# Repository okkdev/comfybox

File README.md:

# 

A stickless fighting game controller, intended to be more ergonomic compared to the regular stickless style layout.

## Features

- Split and 16° angled buttons for improved ergonomics
- Compatible with Kailh Choc v1/v2, Gateron Low Profile 1.0/2.0 and regular MX
- Completely reversible PCB for southpaw layout
- OLED screen
- Powered by [GP2040-CE](https://github.com/OpenStickCommunity/GP2040-CE)
  - Button remapping
  - SOCD Modes
  - XInput, DirectInput and Nintendo Switch
  - Web UI

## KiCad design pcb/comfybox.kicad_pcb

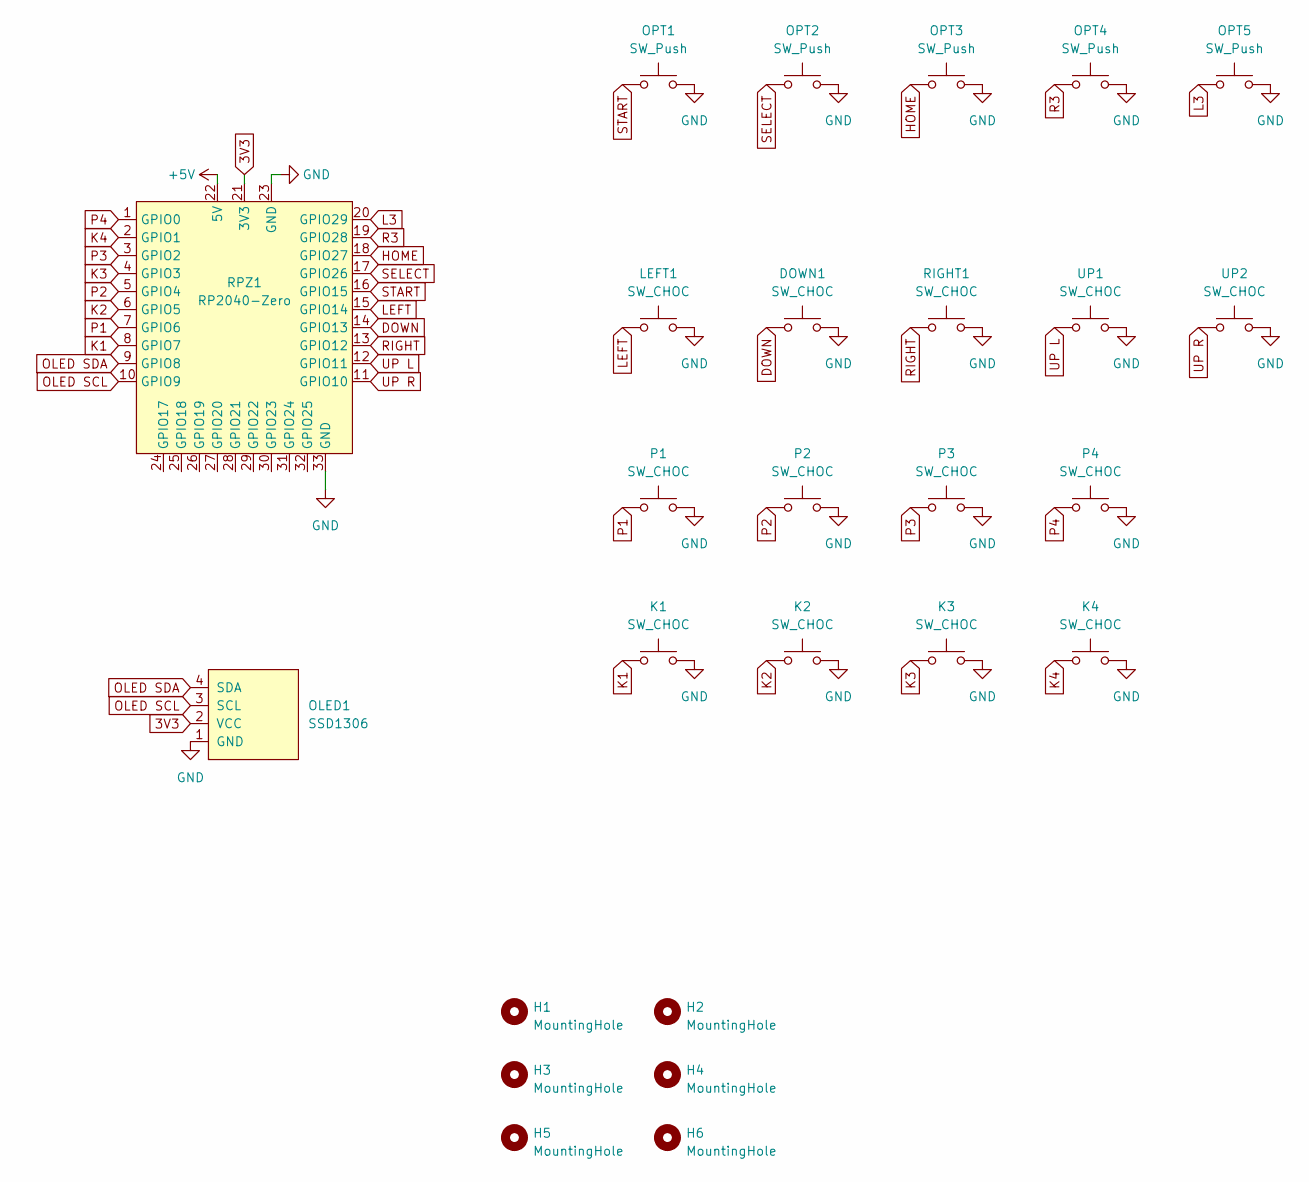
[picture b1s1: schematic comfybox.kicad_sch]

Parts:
DOWN1: SW_CHOC; Kailh_CPG1353_Gateron_KS33_MX_reversible
H1, H2, H3, H4, H5, H6: MountingHole; MountingHole_4mm
K1, K2, K3, K4: SW_CHOC; Kailh_CPG1353_Gateron_KS33_MX_reversible
LEFT1: SW_CHOC; Kailh_CPG1353_Gateron_KS33_MX_reversible
OLED1: SSD1306; SSD1306-128x64_OLED_reversible
OPT1, OPT2, OPT3, OPT4, OPT5: SW_Push; SW_PUSH_6mm
P1, P2, P3, P4: SW_CHOC; Kailh_CPG1353_Gateron_KS33_MX_reversible
RIGHT1: SW_CHOC; Kailh_CPG1353_Gateron_KS33_MX_reversible
RPZ1: RP2040-Zero; RP2040-Zero_reversible_extra
UP1, UP2: SW_CHOC; Kailh_CPG1353_Gateron_KS33_MX_reversible

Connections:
3V3: OLED1.2 (VCC), RPZ1.21 (3V3)
+5V: RPZ1.22 (5V)
DOWN: DOWN1.1, RPZ1.14 (GPIO13)
GND: DOWN1.2, K1.2, K2.2, K3.2, K4.2, LEFT1.2, OLED1.1 (GND), OPT1.2, OPT2.2, OPT3.2, OPT4.2, OPT5.2, P1.2, P2.2, P3.2, P4.2, RIGHT1.2, RPZ1.23 (GND), RPZ1.33 (GND), UP1.2, UP2.2
HOME: OPT3.1, RPZ1.18 (GPIO27)
K1: K1.1, RPZ1.8 (GPIO7)
K2: K2.1, RPZ1.6 (GPIO5)
K3: K3.1, RPZ1.4 (GPIO3)
K4: K4.1, RPZ1.2 (GPIO1)
L3: OPT5.1, RPZ1.20 (GPIO29)
LEFT: LEFT1.1, RPZ1.15 (GPIO14)
OLED SCL: OLED1.3 (SCL), RPZ1.10 (GPIO9)
OLED SDA: OLED1.4 (SDA), RPZ1.9 (GPIO8)
P1: P1.1, RPZ1.7 (GPIO6)
P2: P2.1, RPZ1.5 (GPIO4)
P3: P3.1, RPZ1.3 (GPIO2)
P4: P4.1, RPZ1.1 (GPIO0)
R3: OPT4.1, RPZ1.19 (GPIO28)
RIGHT: RIGHT1.1, RPZ1.13 (GPIO12)
SELECT: OPT2.1, RPZ1.17 (GPIO26)
START: OPT1.1, RPZ1.16 (GPIO15)
UP L: RPZ1.12 (GPIO11), UP1.1
UP R: RPZ1.11 (GPIO10), UP2.1

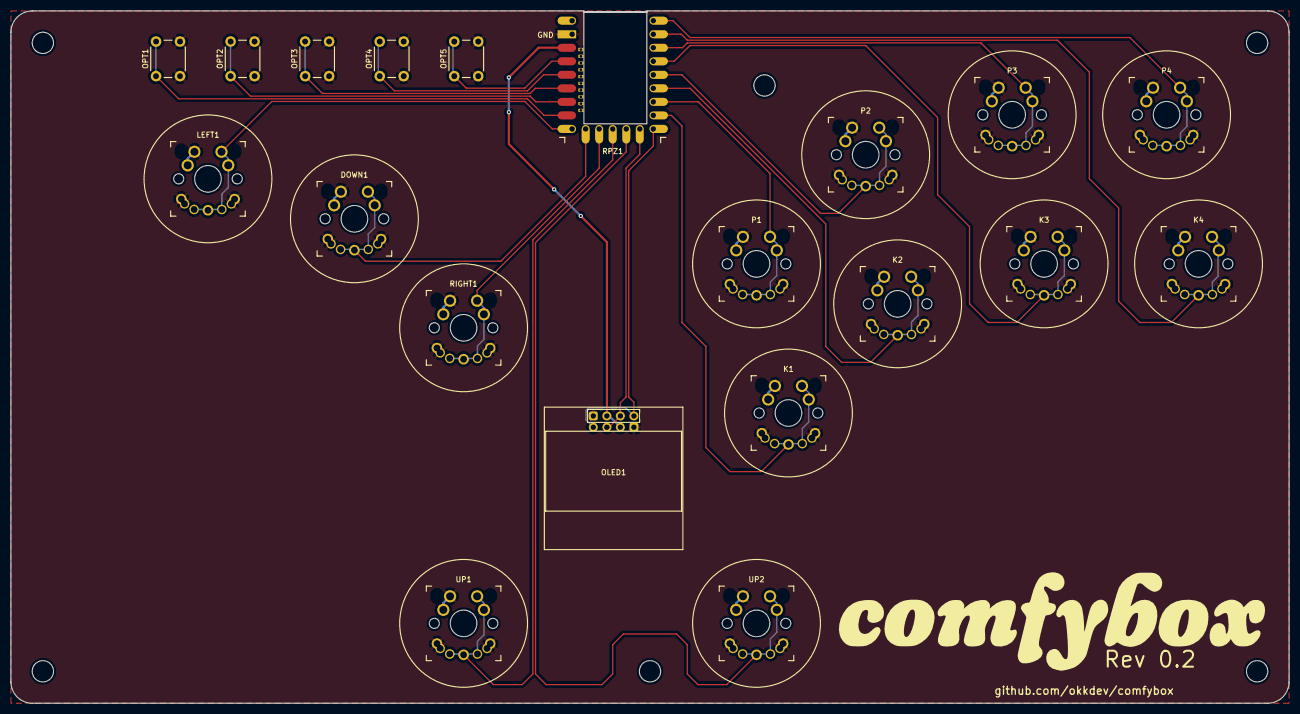
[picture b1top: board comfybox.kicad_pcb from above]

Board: 2 copper layers, 240.0 x 130.0 mm, 28 parts (1 on the bottom side), 22 nets.

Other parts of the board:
LOGO: LOGO
LOGO#2: LOGO

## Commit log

2023-02-08 basic schema
2023-02-08 add basic layout
2023-02-08 fix option button schema
2023-02-08 finished pcb without oled
2023-02-08 add oled
2023-02-09 adjust tracing
2023-02-09 improve spacing and redo tracing
2023-02-10 wip adjusted angle
2023-02-10 update libs and add KS33 support
2023-02-10 remove unused footprint
2023-02-10 cleanup
2023-02-10 remove outdated layout
2023-02-11 add license
2023-02-11 layout experiments
2023-02-13 layout adjustments and MX compatibility
2023-02-13 update description
2023-02-13 add logo and update to kicad7
2023-02-13 redo traces
2023-02-13 remove reference
2023-02-14 add front ground plane
2023-02-14 add logo
2023-02-14 add reversible footprints
2023-02-14 reversible rp2040
2023-02-14 add back oled
2023-02-14 add back silk screen
2023-02-14 rework reversibility
2023-02-16 add mounting holes
2023-02-21 update switch footprint
2023-02-21 update footprints
2023-02-21 add pcb render
2023-02-21 add pcb to readme
2023-02-23 add repo link
2023-02-23 add wip bottom case
2023-02-24 lock all parts and add mounting holes
2023-02-27 move case file
2023-02-27 add top case
2023-02-27 small adjustments
2023-02-27 remade bottom in openscad
2023-02-28 make bottom case configurable for southpaw layout
2023-02-28 add inner layer config to top case
2023-03-03 ignore build folder
2023-03-03 add wristrest to top case
2023-03-03 add gp2040-ce config
2023-03-03 add keycap model
2023-03-04 fix gateron lp orientation
2023-03-08 add more space to pcb cutout
2023-03-08 fix corner radius and button size
2023-03-08 adjust cap sizes
2023-03-08 remove old freescad case
2023-03-08 update rp2040 footprint size
2023-03-08 update rp2040 footprint
2023-03-08 update oled silkscreen
2023-03-08 bump revision
2023-03-08 remove pad from choc v2 3rd pin
2023-03-09 adjust oled cutout size
2023-03-16 adjust option button position
2023-03-16 case stuff...
2023-03-27 wrist rests and adjustments
2023-03-28 adjust ali wrist rest size
2023-03-28 move buttons
2023-04-24 update aliexpress wrist rests
2023-05-22 move bottom row
2023-06-13 fix 3d model
2023-07-17 update license
2023-11-09 add button
2023-11-09 add small case
2023-11-09 update 3d case
2023-11-09 pcb changes
2023-11-22 adjustments
2023-11-23 adjust top 3d
